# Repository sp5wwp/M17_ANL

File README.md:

# M17_ANL  
M17 analyser. May be used for receiving and sending packets over the air (half-duplex).  
  
# Usage  
Communication is realised via UART, 230400 baud, 8 bits of data, no parity, 1 stop bit, no handshake. End of line is \r\n.  
Commands:  
- AT+FREQ?  - shows current frequency (in Hz), default = 439575000  
- AT+PWR?   - shows current power setting, default = 0  

- AT+FREQ=x - sets current frequency (in Hz), range 420..460MHz (inclusively). CAUTION: transmitting signals beyond the amateur band (430..440MHz) may be prohibited by local law.  
- AT+PWR=x  - sets current power setting, range 0 to 127, inclusively. Please refer to the Si4463-C2 datasheet for more information on this.  

- AT+FRAME=x  - sends a 93-byte frame. Replace x with a 93-byte long string ended with \r\n. The device also sends this string upon receiving a correct frame. It also contains 93 bytes of data after the '=' sign. EOL is \r\n as mentioned above.

# Linux software 
Uncomment the *#define PLAYAUDIO* line in main.c and run *make*. Then rename the output with *mv m17_anl m17_anl_audio*.
Comment that line again and run *make clean && make*. Rename the output to *m17_anl_console*.

For recording M17 voice packets use:  
./m17_anl_audio 3.0 > voice.raw  
3.0 is volume value. Alternatively:  
./m17_anl_audio 3.0 | aplay -t raw -f S16_BE -r 8000 -c 1

In both cases, the audio is mono, S16, Big Endian with 8000Hz sample rate.

For received packet list use this command:  
./m17_anl_console  
This will print out all received frames.

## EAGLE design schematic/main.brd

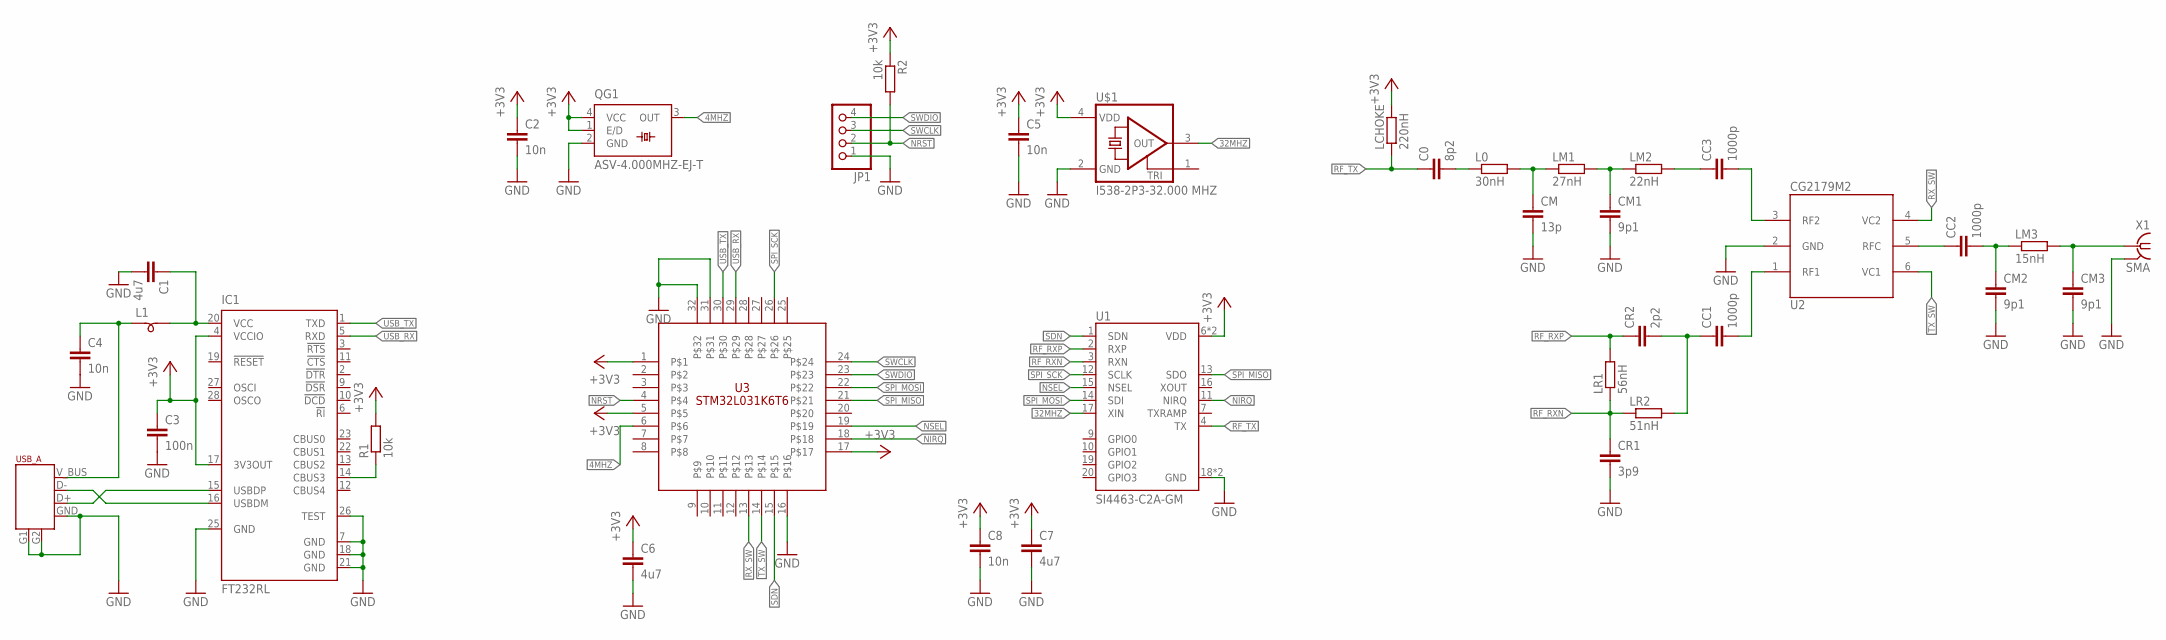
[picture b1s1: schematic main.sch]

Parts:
C0: 8p2; C0805
C1, C6, C7: 4u7; C1206
C2, C4, C5, C8: 10n; C0805
C3: 100n; C0805
CC1, CC2, CC3: 1000p; C0805
CM: 13p; C0805
CM1, CM2, CM3: 9p1; C0805
CR1: 3p9; C0805
CR2: 2p2; C0805
IC1: FT232RL; SSOP28
JP1: PINHD-1X4; 1X04
L0: 30nH; R0805
L1: SM-B5
LCHOKE: 220nH; R0805
LM1: 27nH; R0805
LM2: 22nH; R0805
LM3: 15nH; R0805
LR1: 56nH; R0805
LR2: 51nH; R0805
QG1: ASV-4.000MHZ-EJ-T; SM77H
R1, R2: 10k; R0805
U1: SI4463-C2A-GM; QFN50P400X400X90-20N
U2: CG2179M2; SOT363
U3: STM32L031K6T6; LQFP32-7X7
U$1: I538-2P3-32.000 MHZ; ASE
U$2: USB_TYPE_A; USB_A_THT
X1: SMA; J502-ND-142-0711-821/826

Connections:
4MHZ: QG1.3 (OUT), U3.6
32MHZ: U1.17 (XIN), U$1.3 (OUT)
+3V3: C2.1, C3.1, C5.1, C6.1, C7.1, C8.1, IC1.4 (VCCIO), IC1.17 (3V3OUT), LCHOKE.2, QG1.1 (E/D), QG1.4 (VCC), R1.2, R2.1, U1.6 (VDD), U1.8 (VDD), U3.1, U3.5, U3.17, U$1.4 (VDD)
GND: C1.2, C2.2, C3.2, C4.2, C5.2, C6.2, C7.2, C8.2, CM.2, CM1.2, CM2.2, CM3.2, CR1.2, IC1.7 (GND), IC1.18 (GND), IC1.21 (GND), IC1.25 (GND), IC1.26 (TEST), JP1.1, QG1.2 (GND), U1.18 (GND), U1.21 (GND), U2.2 (GND), U3.16, U3.31, U3.32, U$1.2 (GND), U$2.G1, U$2.G2, U$2.GND, X1.G@1 (2), X1.G@2 (2), X1.G@3 (2), X1.G@4 (2)
unnamed: CC3.1, LM2.2
unnamed: IC1.15 (USBDP), U$2.D+
unnamed: IC1.16 (USBDM), U$2.D-
unnamed: C4.1, L1.1, U$2.V_BUS
unnamed: C1.1, IC1.20 (VCC), L1.2
unnamed: IC1.14 (CBUS3), R1.1
unnamed: CC3.2, U2.3 (RF2)
unnamed: CM3.1, LM3.2, X1.1
unnamed: CC2.2, CM2.1, LM3.1
unnamed: C0.2, L0.1
unnamed: CM.1, L0.2, LM1.1
unnamed: CM1.1, LM1.2, LM2.1
unnamed: CC1.1, CR2.2, LR2.2
unnamed: CC1.2, U2.1 (RF1)
unnamed: CC2.1, U2.5 (RFC)
NIRQ: U1.11 (NIRQ), U3.18
NRST: JP1.2, R2.2, U3.4
NSEL: U1.15 (NSEL), U3.19
RF_RXN: CR1.1, LR1.1, LR2.1, U1.3 (RXN)
RF_RXP: CR2.1, LR1.2, U1.2 (RXP)
RF_TX: C0.1, LCHOKE.1, U1.4 (TX)
RX_SW: U2.4 (VC2), U3.13
SDN: U1.1 (SDN), U3.15
SPI_MISO: U1.13 (SDO), U3.21
SPI_MOSI: U1.14 (SDI), U3.22
SPI_SCK: U1.12 (SCLK), U3.26
SWCLK: JP1.3, U3.24
SWDIO: JP1.4, U3.23
TX_SW: U2.6 (VC1), U3.14
USB_RX: IC1.5 (RXD), U3.29
USB_TX: IC1.1 (TXD), U3.30

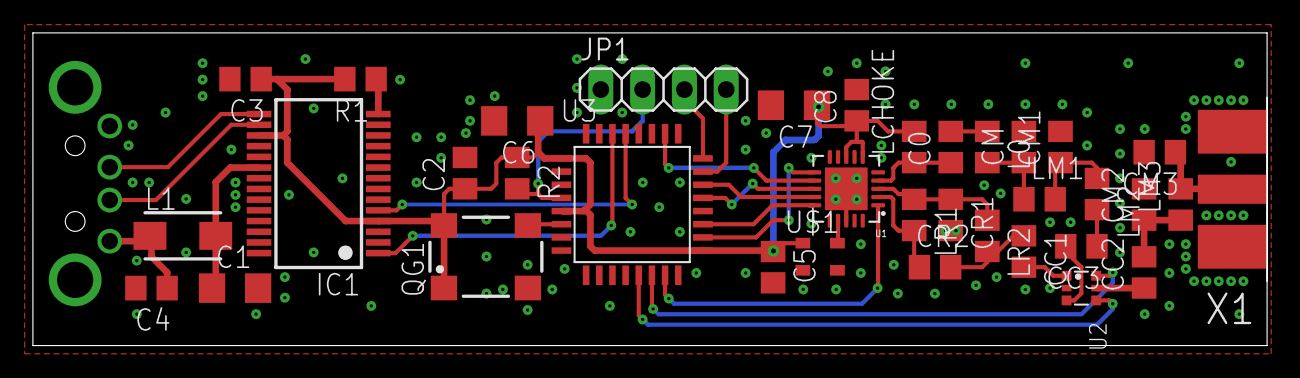
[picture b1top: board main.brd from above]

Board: 2 copper layers, 75.0 x 19.0 mm, 37 parts (0 on the bottom side), 35 nets.

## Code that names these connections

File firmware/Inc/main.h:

/**
  ******************************************************************************
  * @file           : main.h
  * @brief          : Header for main.c file.
  *                   This file contains the common defines of the application.
  ******************************************************************************
  ** This notice applies to any and all portions of this file
  * that are not between comment pairs USER CODE BEGIN and
  * USER CODE END. Other portions of this file, whether 
  * inserted by the user or by software development tools
  * are owned by their respective copyright owners.
  *
  * COPYRIGHT(c) 2019 STMicroelectronics
  *
  * Redistribution and use in source and binary forms, with or without modification,
  * are permitted provided that the following conditions are met:
  *   1. Redistributions of source code must retain the above copyright notice,
  *      this list of conditions and the following disclaimer.
  *   2. Redistributions in binary form must reproduce the above copyright notice,
  *      this list of conditions and the following disclaimer in the documentation
  *      and/or other materials provided with the distribution.
  *   3. Neither the name of STMicroelectronics nor the names of its contributors
  *      may be used to endorse or promote products derived from this software
  *      without specific prior written permission.
  *
  * THIS SOFTWARE IS PROVIDED BY THE COPYRIGHT HOLDERS AND CONTRIBUTORS "AS IS"
  * AND ANY EXPRESS OR IMPLIED WARRANTIES, INCLUDING, BUT NOT LIMITED TO, THE
  * IMPLIED WARRANTIES OF MERCHANTABILITY AND FITNESS FOR A PARTICULAR PURPOSE ARE
  * DISCLAIMED. IN NO EVENT SHALL THE COPYRIGHT HOLDER OR CONTRIBUTORS BE LIABLE
  * FOR ANY DIRECT, INDIRECT, INCIDENTAL, SPECIAL, EXEMPLARY, OR CONSEQUENTIAL
  * DAMAGES (INCLUDING, BUT NOT LIMITED TO, PROCUREMENT OF SUBSTITUTE GOODS OR
  * SERVICES; LOSS OF USE, DATA, OR PROFITS; OR BUSINESS INTERRUPTION) HOWEVER
  * CAUSED AND ON ANY THEORY OF LIABILITY, WHETHER IN CONTRACT, STRICT LIABILITY,
  * OR TORT (INCLUDING NEGLIGENCE OR OTHERWISE) ARISING IN ANY WAY OUT OF THE USE
  * OF THIS SOFTWARE, EVEN IF ADVISED OF THE POSSIBILITY OF SUCH DAMAGE.
  *
  ******************************************************************************
  */

/* Define to prevent recursive inclusion -------------------------------------*/
#ifndef __MAIN_H__
#define __MAIN_H__

/* Includes ------------------------------------------------------------------*/

/* USER CODE BEGIN Includes */

/* USER CODE END Includes */

/* Private define ------------------------------------------------------------*/

#define RX_SW_Pin GPIO_PIN_7
#define RX_SW_GPIO_Port GPIOA
#define TX_SW_Pin GPIO_PIN_0
#define TX_SW_GPIO_Port GPIOB
#define TRX_SDN_Pin GPIO_PIN_1
#define TRX_SDN_GPIO_Port GPIOB
#define NIRQ_Pin GPIO_PIN_8
#define NIRQ_GPIO_Port GPIOA
#define NIRQ_EXTI_IRQn EXTI4_15_IRQn
#define NSEL_Pin GPIO_PIN_9
#define NSEL_GPIO_Port GPIOA

/* ########################## Assert Selection ############################## */
/**
  * @brief Uncomment the line below to expanse the "assert_param" macro in the 
  *        HAL drivers code
  */
/* #define USE_FULL_ASSERT    1U */

/* USER CODE BEGIN Private defines */

/* USER CODE END Private defines */

#ifdef __cplusplus
 extern "C" {
#endif
void _Error_Handler(char *, int);

#define Error_Handler() _Error_Handler(__FILE__, __LINE__)
#ifdef __cplusplus
}
#endif

#endif /* __MAIN_H__ */

/************************ (C) COPYRIGHT STMicroelectronics *****END OF FILE****/

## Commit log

2019-07-16 Add files via upload
    updated byte locations
